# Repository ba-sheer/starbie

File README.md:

# starbie
this is my project for week 1 of halflife ysws.my goal is to build a keychain tamagotchi based on guide provided by hc

this is the link of half life project page https://halflife.hackclub.com/projects/cmuyamfi1004z01qvesjx09nr

The idea is simple: take care of a tiny digital pet by feeding it, playing with it, and shaking the device to interact with it. An OLED screen displays the pet, while RGB LEDs show its current status.

I'm using a Seeed Studio XIAO ESP32-C3 as the main controller, along with an OLED display, an MPU6050 for motion detection, buttons, and a few other components.

this project is basicly a tamagothchi i am planning to use as my backpacks key chain and It is week 1 of learning the hardware series

fully funded by hackclub

# bom

| Item                     | Qty | Supplier      | Cost/item | Total Cost | link                                                                                                                       |
|--------------------------|-----|---------------|-----------|------------|----------------------------------------------------------------------------------------------------------------------------|
| XIAO ESP32-C3            | 1   | techism       | $6.00     | $6.00      | https://techiesms.com/product/seeed-studio-xiao-esp32c3/?srsltid=AU7gw4X0ypi5G6QPsjTj6_fCxW_KTHcVgSjSWs9jFoDQ4cQplrFg8Iaqx |
| Mechanical switches      | 1   | cosmic byte   | $4.12     | $4.12      | https://www.thecosmicbyte.com/product/outemu-mechanical-switches-for-swappable-keyboards-pack-of-20/                       |
| OLED display             | 1   | techism       | $2.00     | $2.00      | https://techiesms.com/product/0-96-inch-i2c-iic-4pin-128x64-oled-disp/                                                     |
| MPU6050 module           | 1   | techism       | $2.00     | $2.00      | https://techiesms.com/product/mpu6050-3-axis-accelerometer-and-gyro-sensor/                                                |
| dht11                    | 1   | robocraze     | $0.70     | $0.70      | https://robocraze.com/products/dht11-humidity-and-temperature-sensor                                                       |
| passive buzzer           | 1   | quartz        | $0.70     | $0.70      | https://quartzcomponents.com/products/piezo-buzzer                                                                         |
| pcb                      | 1   | jlcpcb        | $9.00     | $9.00      | https://jlcpcb.com                                                                                                         |
| key and switches         | 1   | unknown       | $0.00     | $0.00      | https://meckeys.com/shop/accessories/keyboard-accessories/key-switches/gateron-5-pin-switch-tester-pack/                   |
| resistor                 | 1   | already owned | $0.00     | $0.00      | https://www.amazon.in/DEPOKE-Value-Resistor-Pack-320pcs/dp/B0CGY55MDP/                                                     |
| leds                     | 1   | robocraze     | $0.30     | $0.30      | https://robocraze.com/products/ws2812-8-bit-rgb-led-straight                                                               |
| Estimated total shipping | 1   |               | $4.00     | $4.00      |                                                                                                                            |
| TOTAL                    |     |               |           | $28.82     |                                                                                                                            |

## Controls

| Input | Action |
|---|---|
| Feed button  | Feed the pet |
| Play button | Play with the pet |
| Shake device | Interact with the pet |

## LED Indicators

| Color | Status |
|---|---|
| Red | Pet is dead |
| Orange | Low hunger |
| Green | High happiness |
| Blue | Normal |

# COMPONENTS

| Component | Quantity |
|---|---:|
| Seeed Studio XIAO ESP32-C3 | 1 |
| 128×64 I²C OLED | 1 |
| DHT11 | 1 |
| MPU6050 | 1 |
| Passive buzzer | 1 |
| WS2812B | 3 |
| MX-style switches | 2 |
| PCB | 1 |

| Function | ESP32-C3 GPIO | XIAO Pin |
|---|---:|---:|
| OLED SDA | GPIO6 | D4 |
| OLED SCL | GPIO7 | D5 |
| DHT11 DATA | GPIO3 | D1 |
| Feed button | GPIO4 | D2 |
| Play button | GPIO5 | D3 |
| WS2812B DIN | GPIO21 | D6 |
| Passive buzzer | GPIO10 | D10 |
| MPU6050 SDA | GPIO6 | D4 |
| MPU6050 SCL | GPIO7 | D5 |

I²C Addresses
```
OLED      0x3C
MPU6050   0x68
```
thanks to hack club and zach latta

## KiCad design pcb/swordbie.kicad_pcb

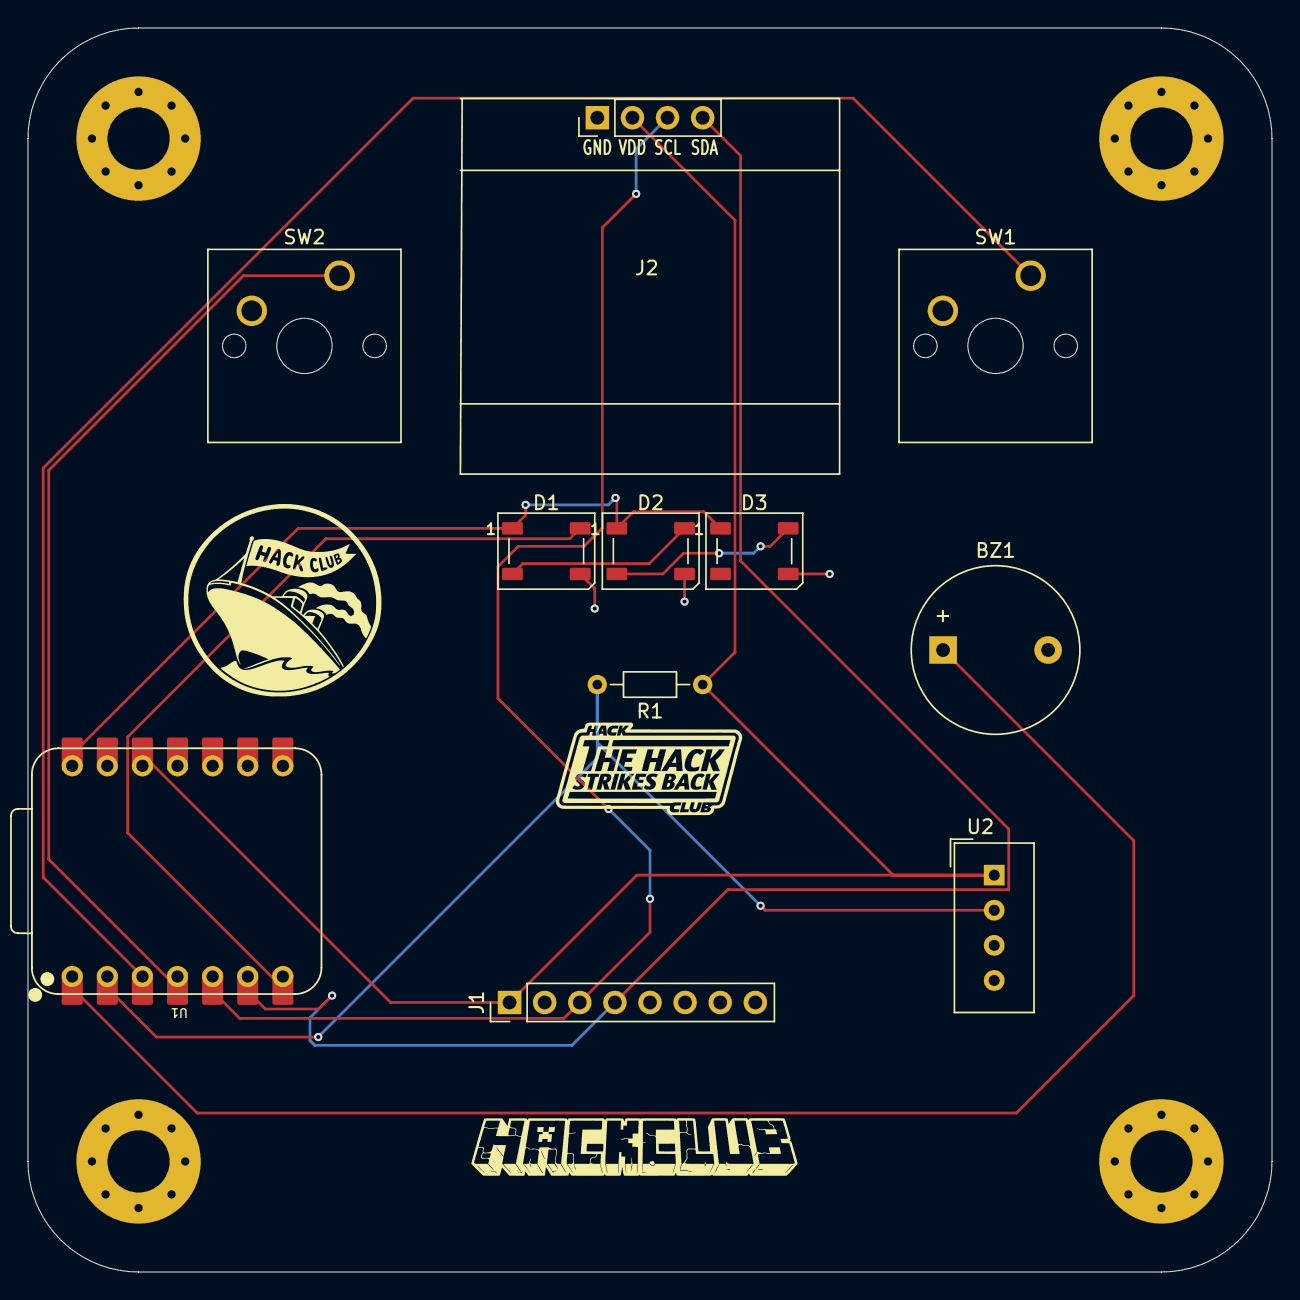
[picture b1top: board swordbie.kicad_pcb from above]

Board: 2 copper layers, 90.0 x 90.0 mm, 11 parts (0 on the bottom side), 12 nets.

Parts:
BZ1: Buzzer; Buzzer_12x9.5RM7.6
D1, D2, D3: WS2812B; LED_WS2812B_PLCC4_5.0x5.0mm_P3.2mm
J1: Conn_01x08_Pin; PinHeader_1x08_P2.54mm_Vertical
J2: Conn_01x04_Pin; Display_128x64_096_I2C
R1: R; R_Axial_DIN0204_L3.6mm_D1.6mm_P7.62mm_Horizontal
SW1, SW2: SW_Push; SW_Cherry_MX_1.00u_PCB
U1: XIAO-ESP32-C3-SMD; XIAO-ESP32-C6-DIP
U2: DHT11; Aosong_DHT11_5.5x12.0_P2.54mm

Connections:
+3.3V: J1.1, J2.2, R1.1, U1.12 (3V3_OUT), U2.1 (VDD)
/5V: D1.1 (VDD), D2.1 (VDD), D3.1 (VDD), U1.14 (VBUS)
/DHT11 DATA: R1.2, U1.2 (D1), U2.2 (DATA)
/DIN: D1.4 (DIN), U1.7 (D6)
/GPI00: BZ1.1 (+), U1.1 (D0)
/GPI02: SW1.1, U1.3 (D2)
/GPI03: SW2.1, U1.4 (D3)
/SCL: J1.3, J2.3, U1.5 (D4)
/SDA: J1.4, J2.4, U1.6 (D5)
GND: BZ1.2 (-), D1.3 (VSS), D2.3 (VSS), D3.3 (VSS), J1.2, J2.1, SW1.2, SW2.2, U1.13 (GND), U2.4 (GND)
unnamed: D1.2 (DOUT), D2.4 (DIN)
unnamed: D2.2 (DOUT), D3.4 (DIN)
